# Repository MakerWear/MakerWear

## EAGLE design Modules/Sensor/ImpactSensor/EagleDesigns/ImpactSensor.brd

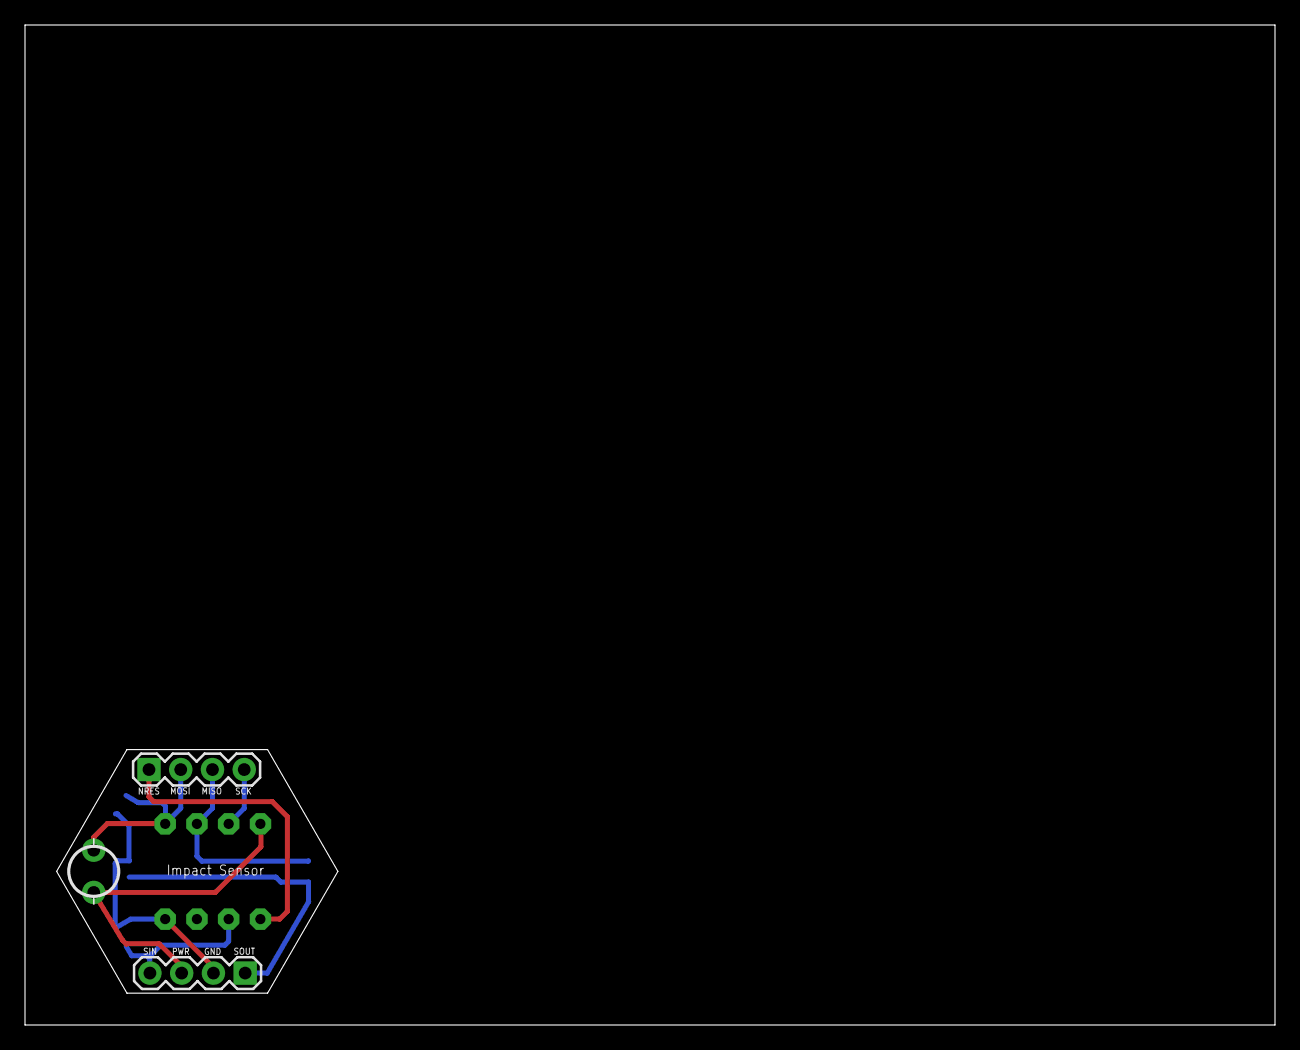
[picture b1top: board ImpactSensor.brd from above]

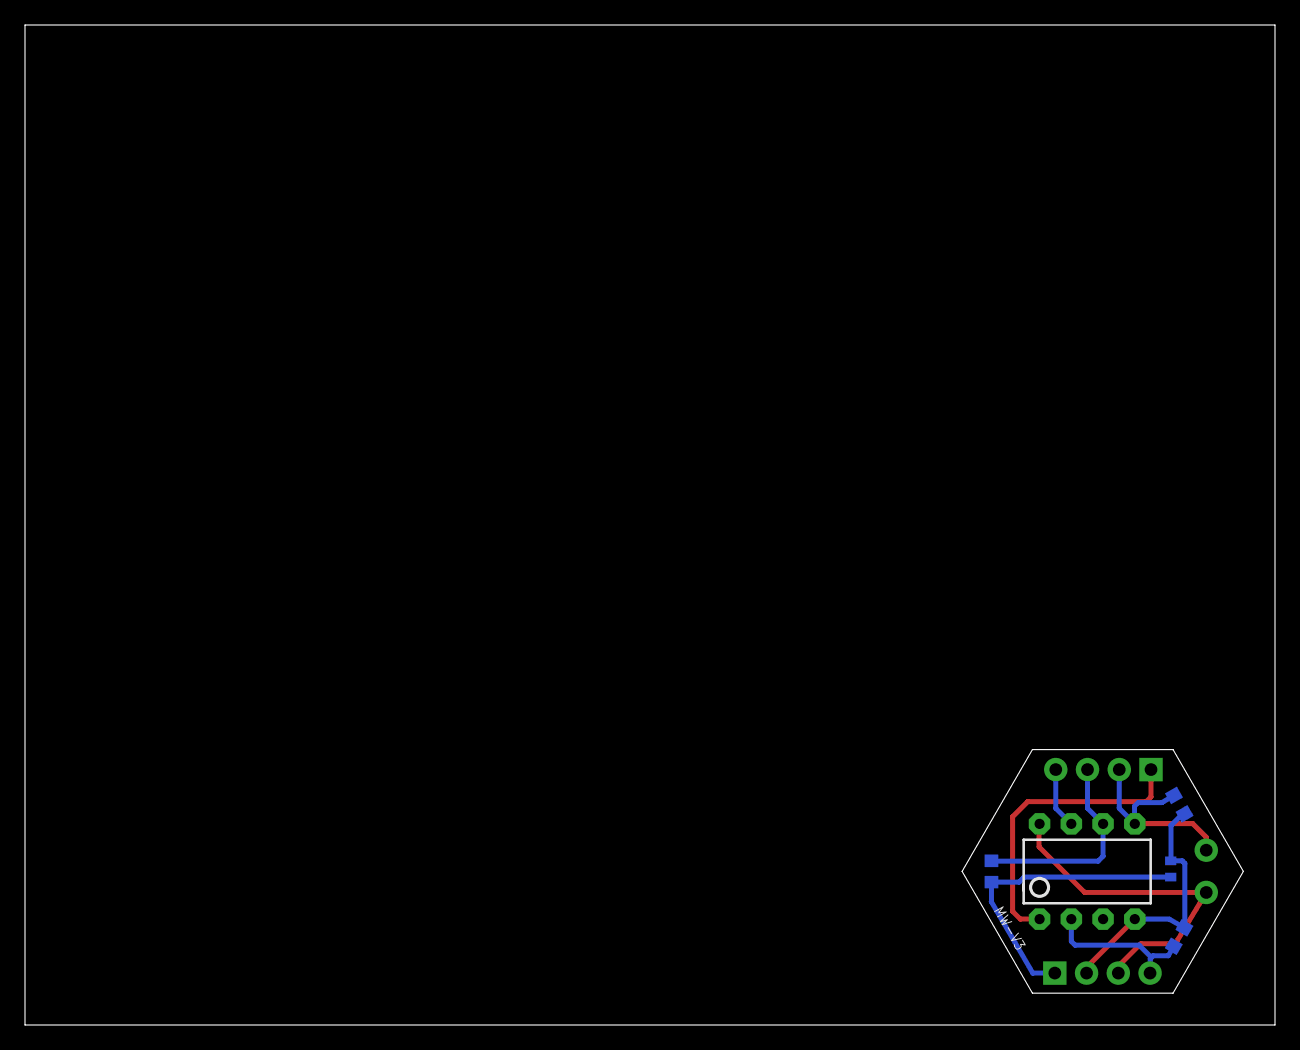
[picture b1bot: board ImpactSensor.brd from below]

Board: 2 copper layers, 100.0 x 80.0 mm, 8 parts (5 on the bottom side), 8 nets.

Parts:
C1: 0.22uF; C0402
JP1, JP2: 1X04
R1: 1M; R0603
R2: 330K; R0603
R3: 4.7K; R0603
TILT1: TILT-AT407
U2: TINY85-20-DIP; DIP08

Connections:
1X3SIN: JP1.4, R1.2, U2.2
1X3SOUT: C1.2, JP1.1, R3.1
GND: C1.1, JP1.2, R1.1, R2.1, U2.4
NRES: JP2.1, U2.1
OUT(MISO): JP2.3, R3.2, U2.6
SCK: JP2.4, U2.7
SENSOR(MOSI): JP2.2, R2.2, TILT1.P$2, U2.5
VCC: JP1.3, TILT1.P$1, U2.8

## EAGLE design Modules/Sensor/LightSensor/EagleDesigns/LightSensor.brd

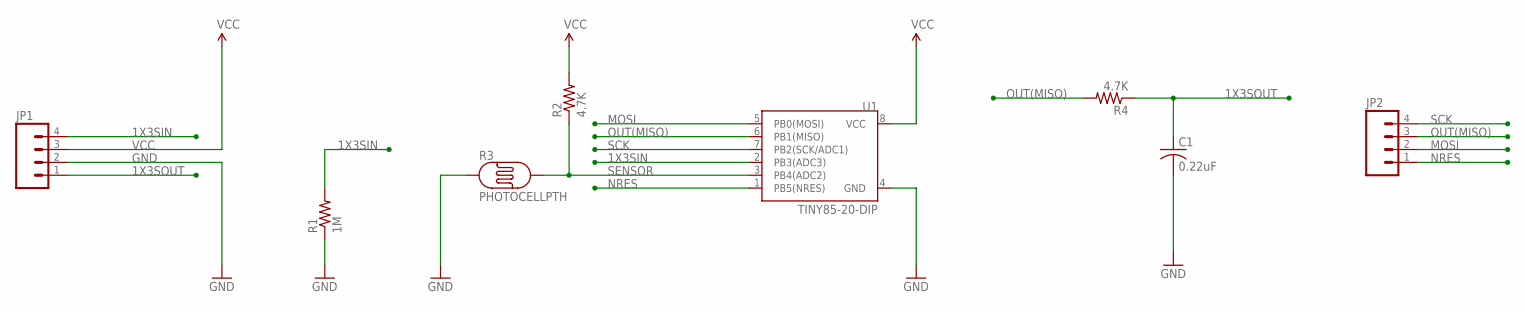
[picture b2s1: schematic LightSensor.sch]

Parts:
C1: 0.22uF; C0402
JP1, JP2: M04PTH; 1X04
R1: 1M; R0603
R2, R4: 4.7K; R0603
R3: PHOTOCELLPTH; PHOTOCELL
U1: TINY85-20-DIP; DIP08

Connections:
1X3SIN: JP1.4, R1.2, U1.2 (PB3(ADC3))
1X3SOUT: C1.1, JP1.1, R4.1
GND: C1.2, JP1.2, R1.1, R3.1, U1.4 (GND)
MOSI: JP2.2, U1.5 (PB0(MOSI))
NRES: JP2.1, U1.1 (PB5(NRES))
OUT(MISO): JP2.3, R4.2, U1.6 (PB1(MISO))
SCK: JP2.4, U1.7 (PB2(SCK/ADC1))
SENSOR: R2.1, R3.2, U1.3 (PB4(ADC2))
VCC: JP1.3, R2.2, U1.8 (VCC)

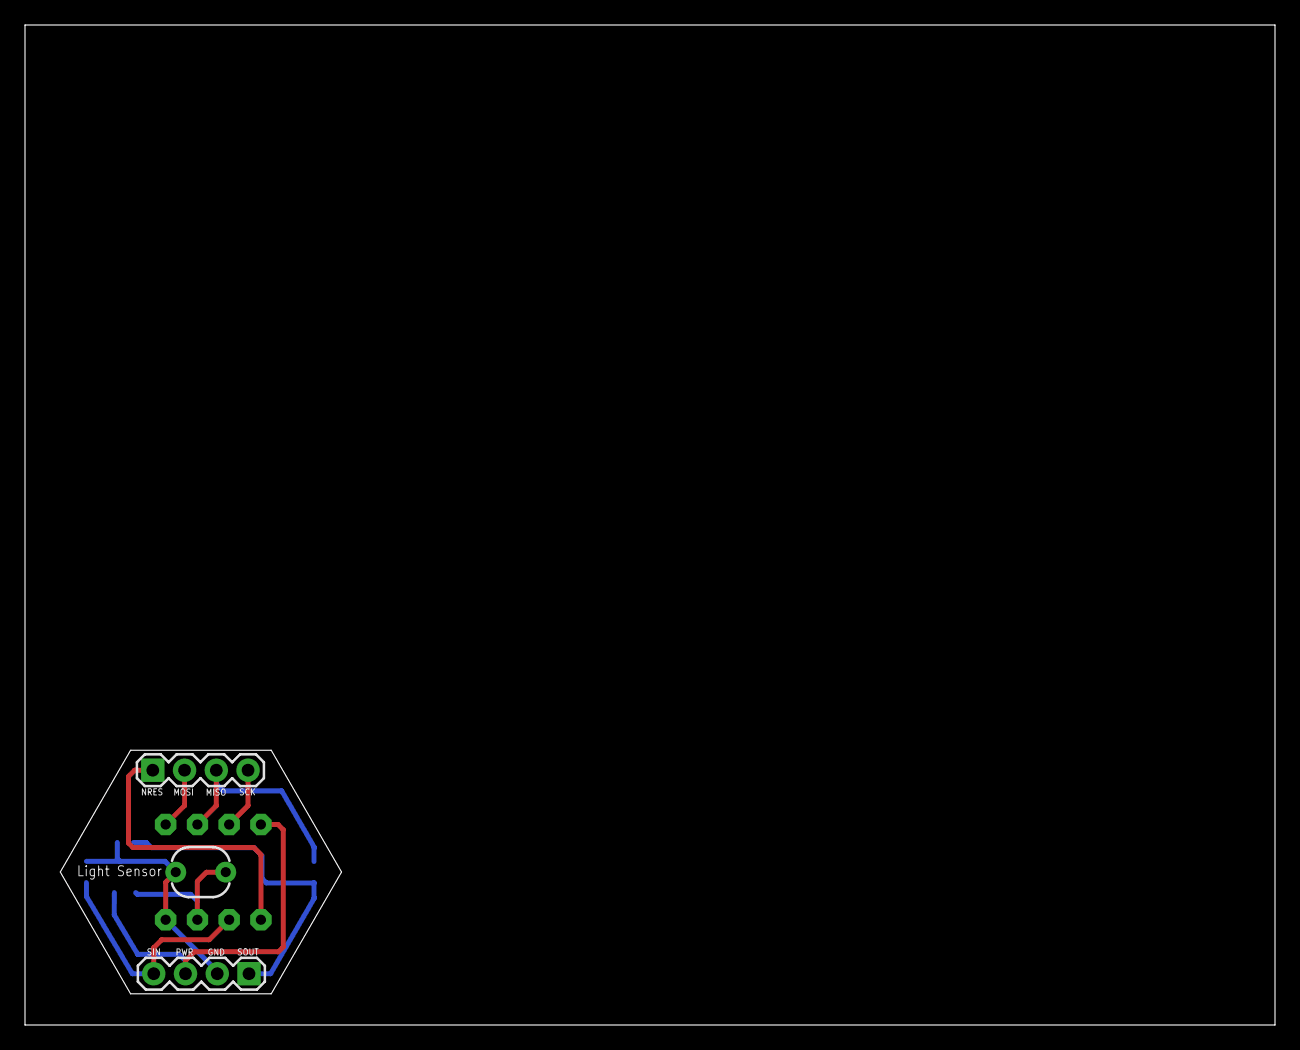
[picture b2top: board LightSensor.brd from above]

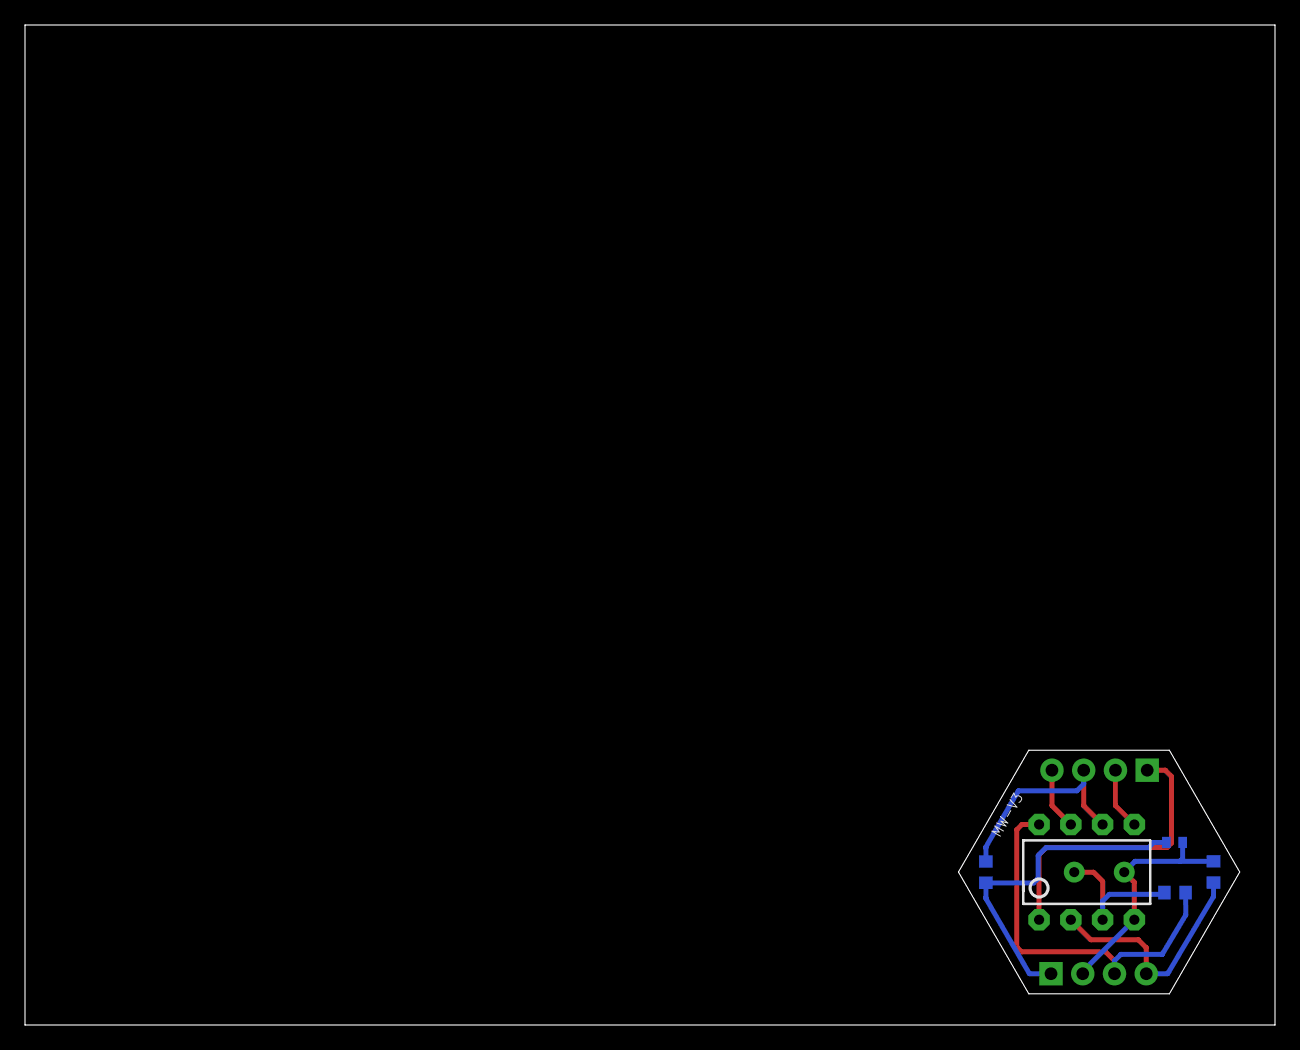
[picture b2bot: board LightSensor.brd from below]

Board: 2 copper layers, 100.0 x 80.0 mm, 8 parts (5 on the bottom side), 9 nets.

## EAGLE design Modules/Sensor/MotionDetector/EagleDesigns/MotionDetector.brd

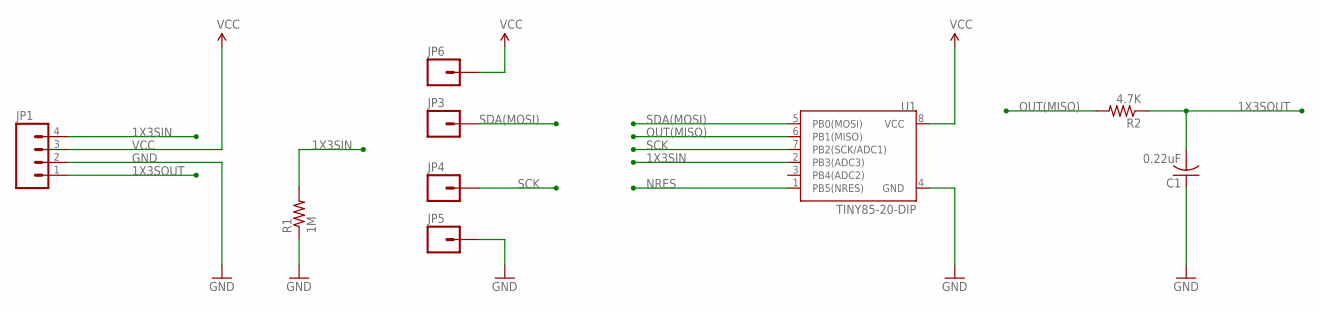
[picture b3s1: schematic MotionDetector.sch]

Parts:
C1: 0.22uF; C0402
JP1: M04PTH; 1X04
JP3, JP4, JP5, JP6: M01PTH; 1X01
R1: 1M; R0603
R2: 4.7K; R0603
U1: TINY85-20-DIP; DIP08

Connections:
1X3SIN: JP1.4, R1.2, U1.2 (PB3(ADC3))
1X3SOUT: C1.2, JP1.1, R2.1
GND: C1.1, JP1.2, JP5.1, R1.1, U1.4 (GND)
NRES: U1.1 (PB5(NRES))
OUT(MISO): R2.2, U1.6 (PB1(MISO))
SCK: JP4.1, U1.7 (PB2(SCK/ADC1))
SDA(MOSI): JP3.1, U1.5 (PB0(MOSI))
VCC: JP1.3, JP6.1, U1.8 (VCC)

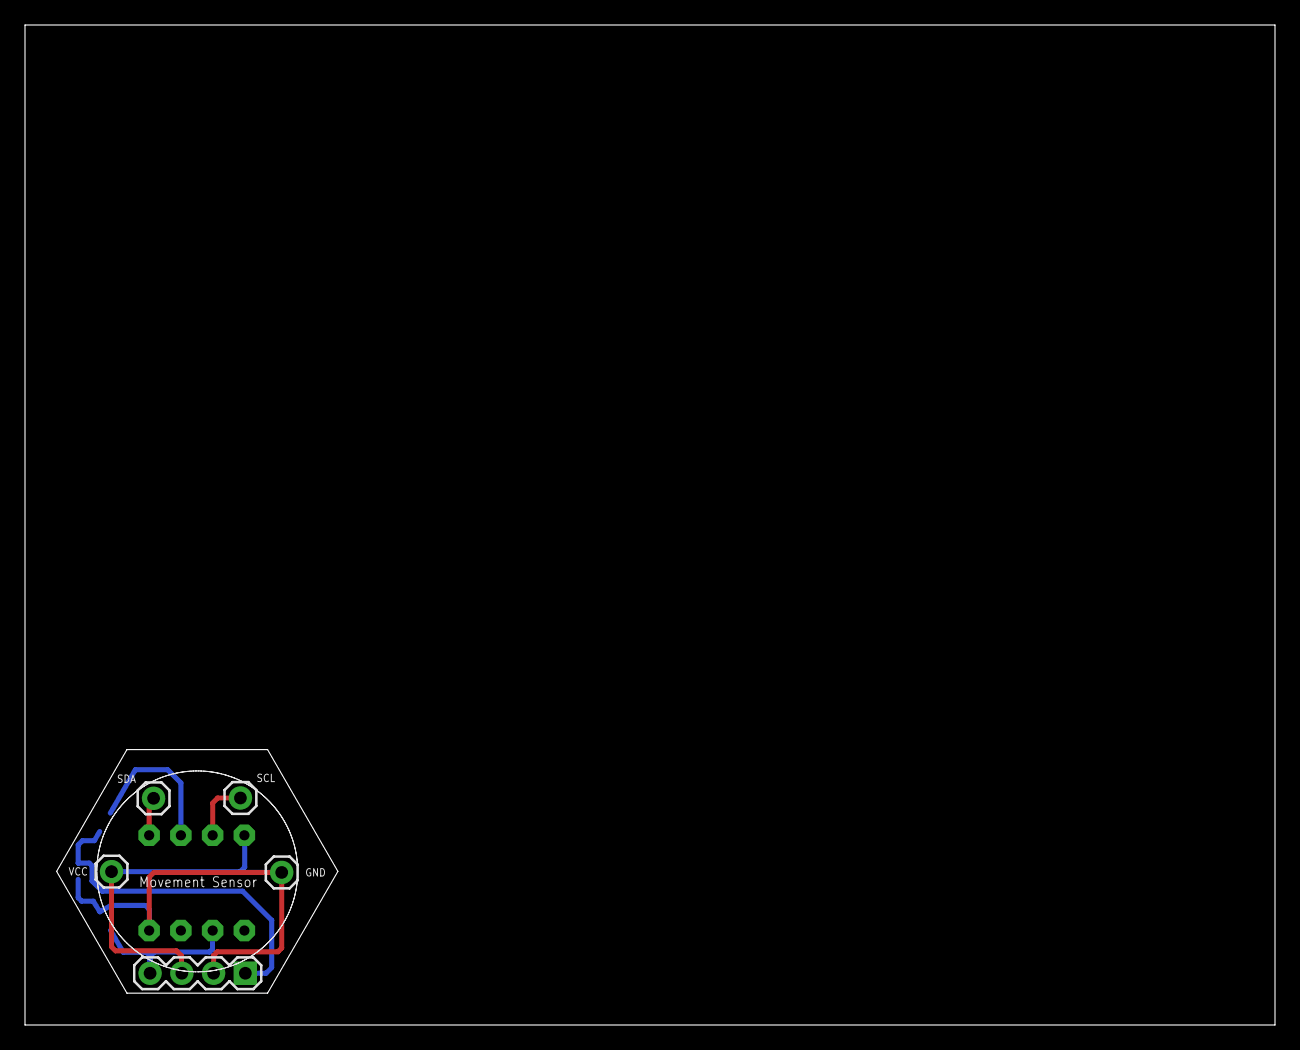
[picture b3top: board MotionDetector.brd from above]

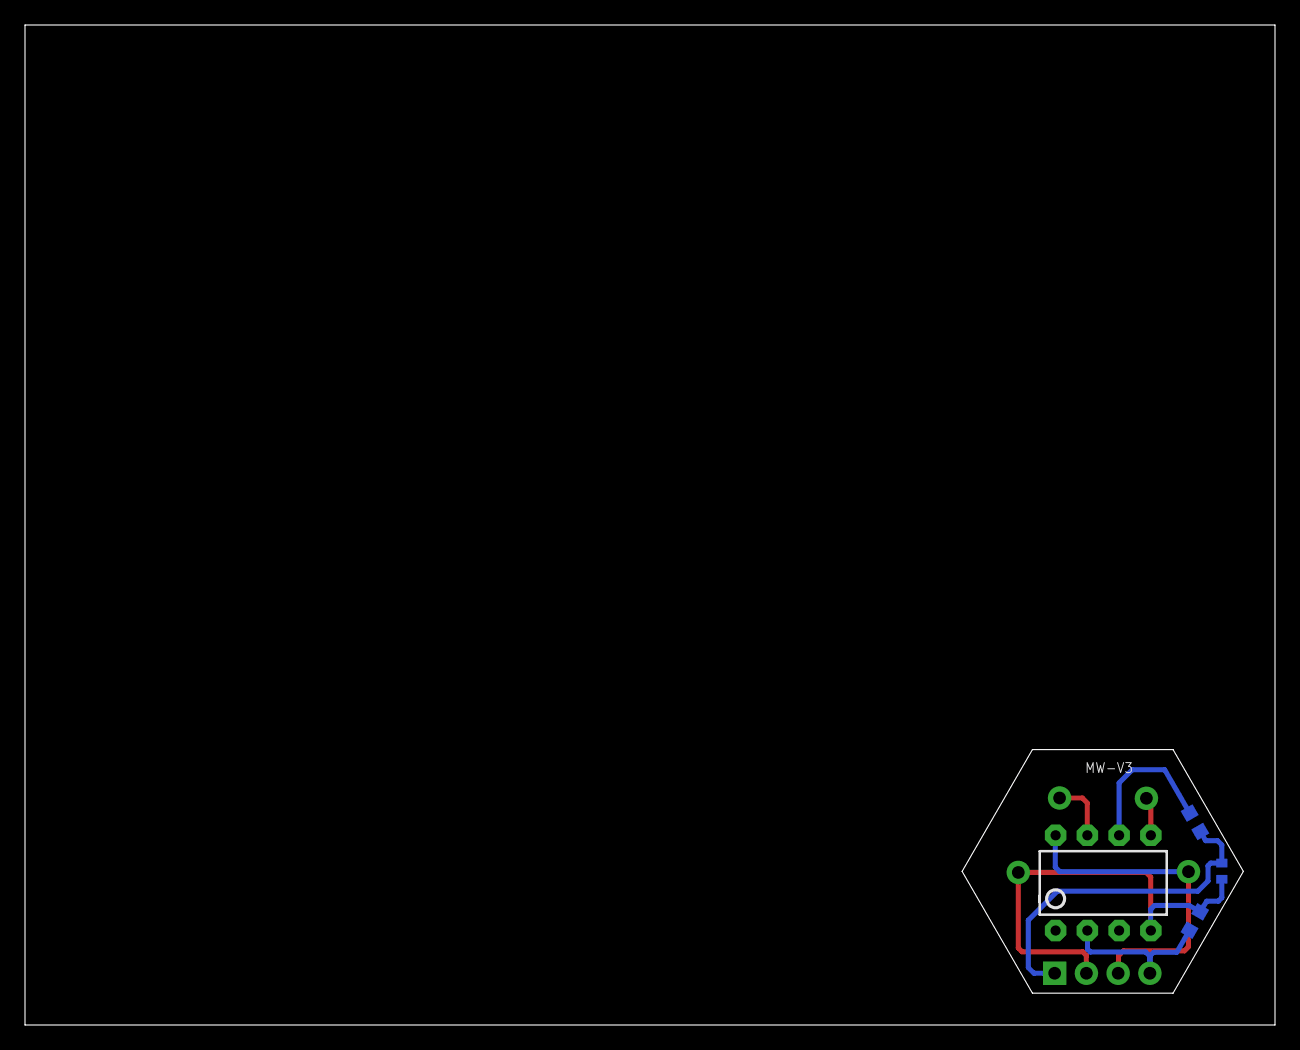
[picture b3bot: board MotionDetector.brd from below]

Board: 2 copper layers, 100.0 x 80.0 mm, 9 parts (4 on the bottom side), 7 nets.

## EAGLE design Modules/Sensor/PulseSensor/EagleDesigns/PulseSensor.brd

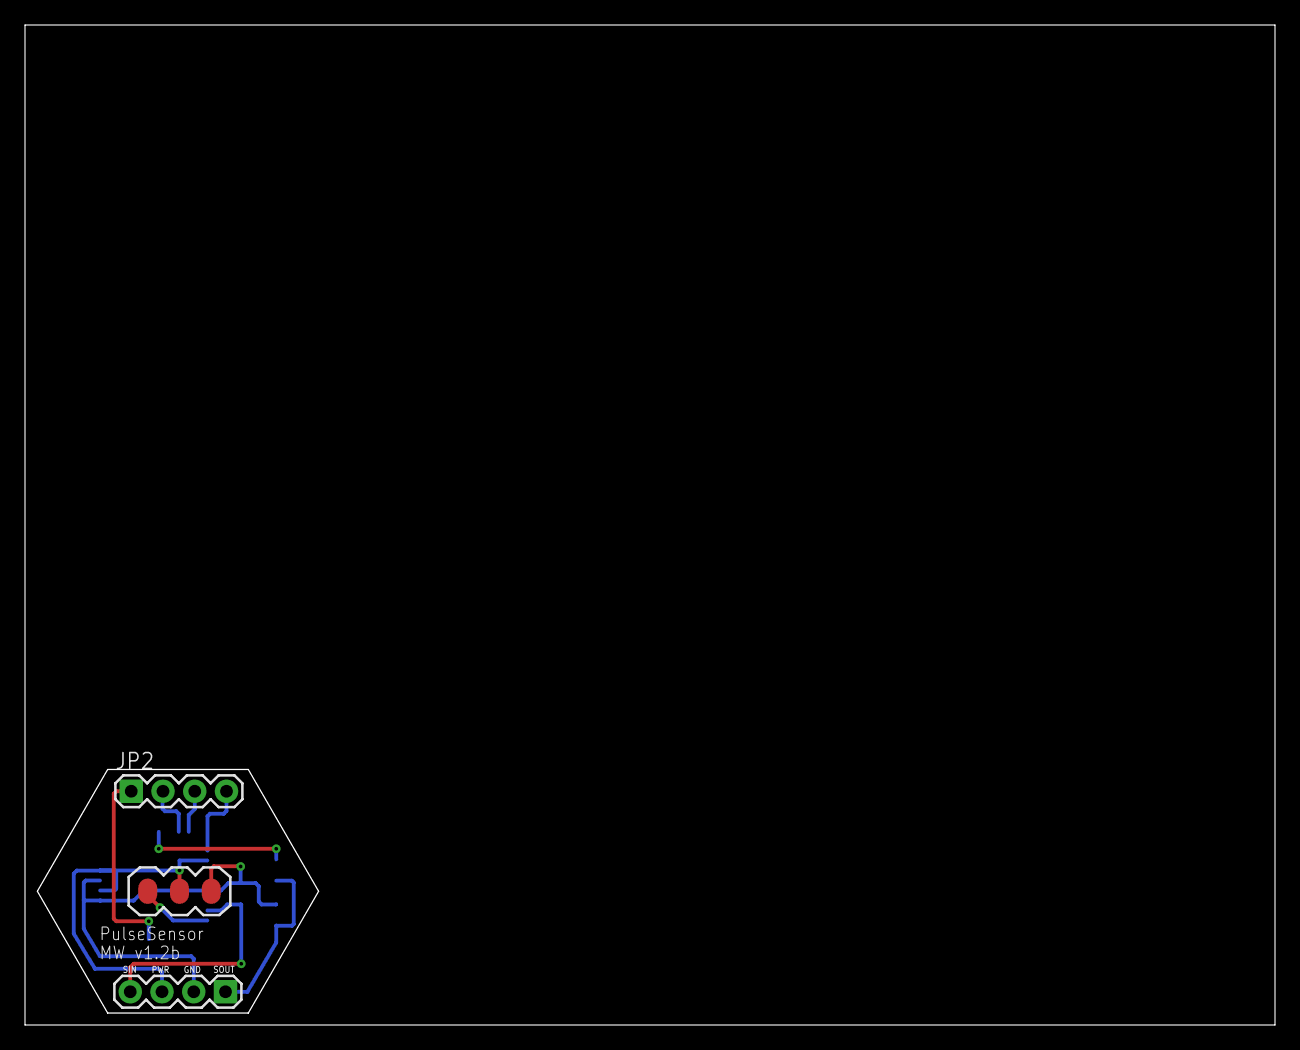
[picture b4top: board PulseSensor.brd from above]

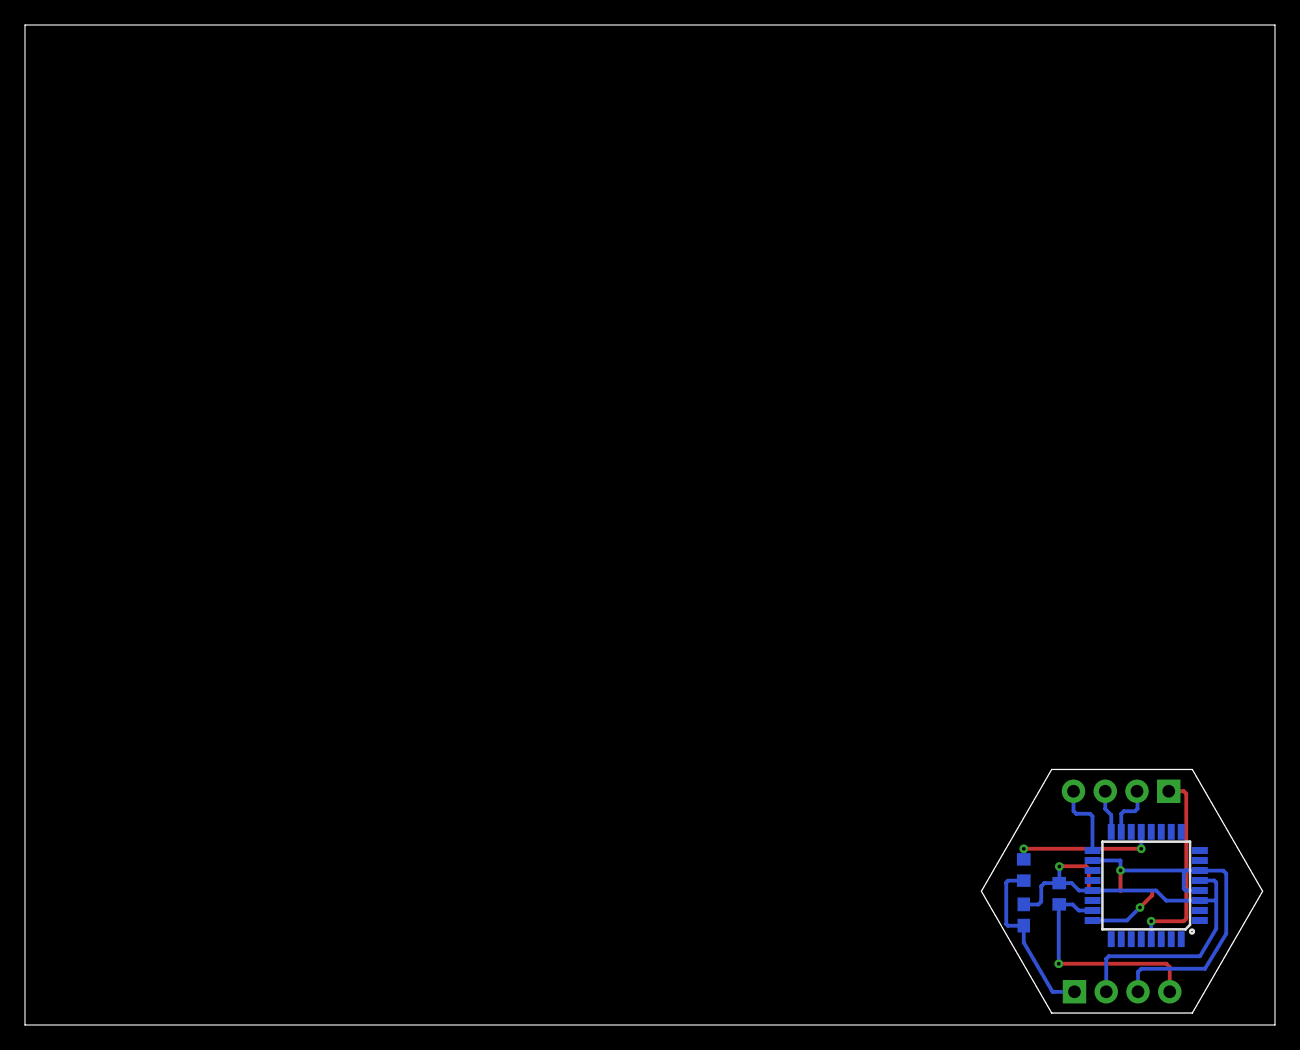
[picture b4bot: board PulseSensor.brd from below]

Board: 2 copper layers, 100.0 x 80.0 mm, 7 parts (4 on the bottom side), 10 nets.

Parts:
C3: 0.22uF; C0603
JP1, JP2: 1X04
JP3: 1X03_NO_HOLES
R1: 1M; R0603
R4: 4.7K; R0603
U2: ATMEGA328P_TQFP; TQFP32-08

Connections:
1X3SIN: JP1.4, R1.2, U2.23
1X3SOUT: C3.1, JP1.1, R4.1
GND: C3.2, JP1.2, JP3.1, R1.1, U2.3, U2.5, U2.21
MISO: JP2.3, U2.16
MOSI: JP2.2, U2.15
OUT: R4.2, U2.13
PULSE-IN: JP3.3, U2.24
RESET: JP2.1, U2.29
SCK: JP2.4, U2.17
VCC: JP1.3, JP3.2, U2.4, U2.6, U2.18

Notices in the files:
parts and their libraries:
SparkFun-Connectors: Licensing: Creative Commons ShareAlike 4.0 International - https://creativecommons.org/licenses/by-sa/4.0
